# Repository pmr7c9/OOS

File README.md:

# OOS
	OOS - optyczny odbiornik sygnałów
	Urządzenie do odbioru sygnału optycznego i konwersję na sygnał elektryczny.

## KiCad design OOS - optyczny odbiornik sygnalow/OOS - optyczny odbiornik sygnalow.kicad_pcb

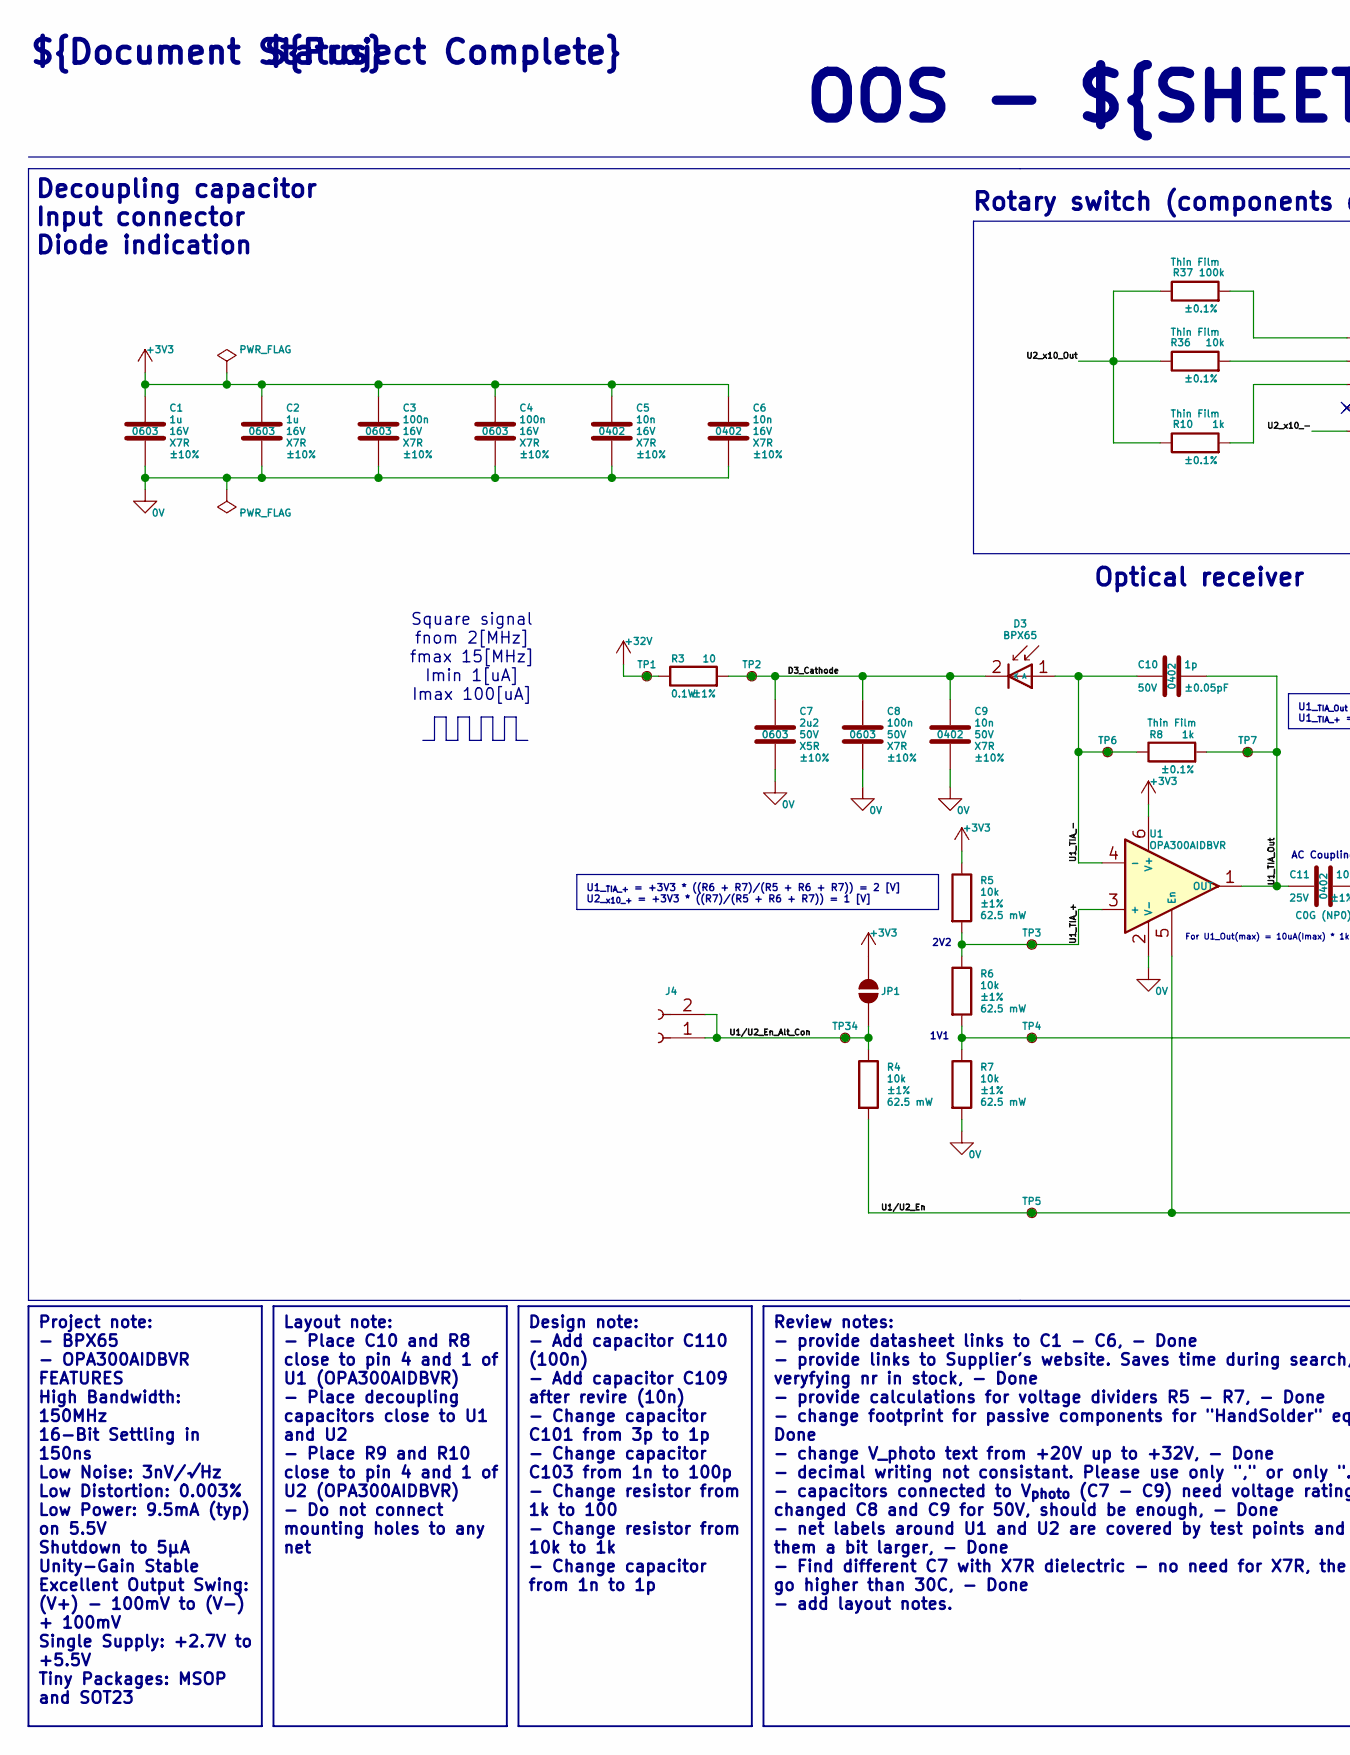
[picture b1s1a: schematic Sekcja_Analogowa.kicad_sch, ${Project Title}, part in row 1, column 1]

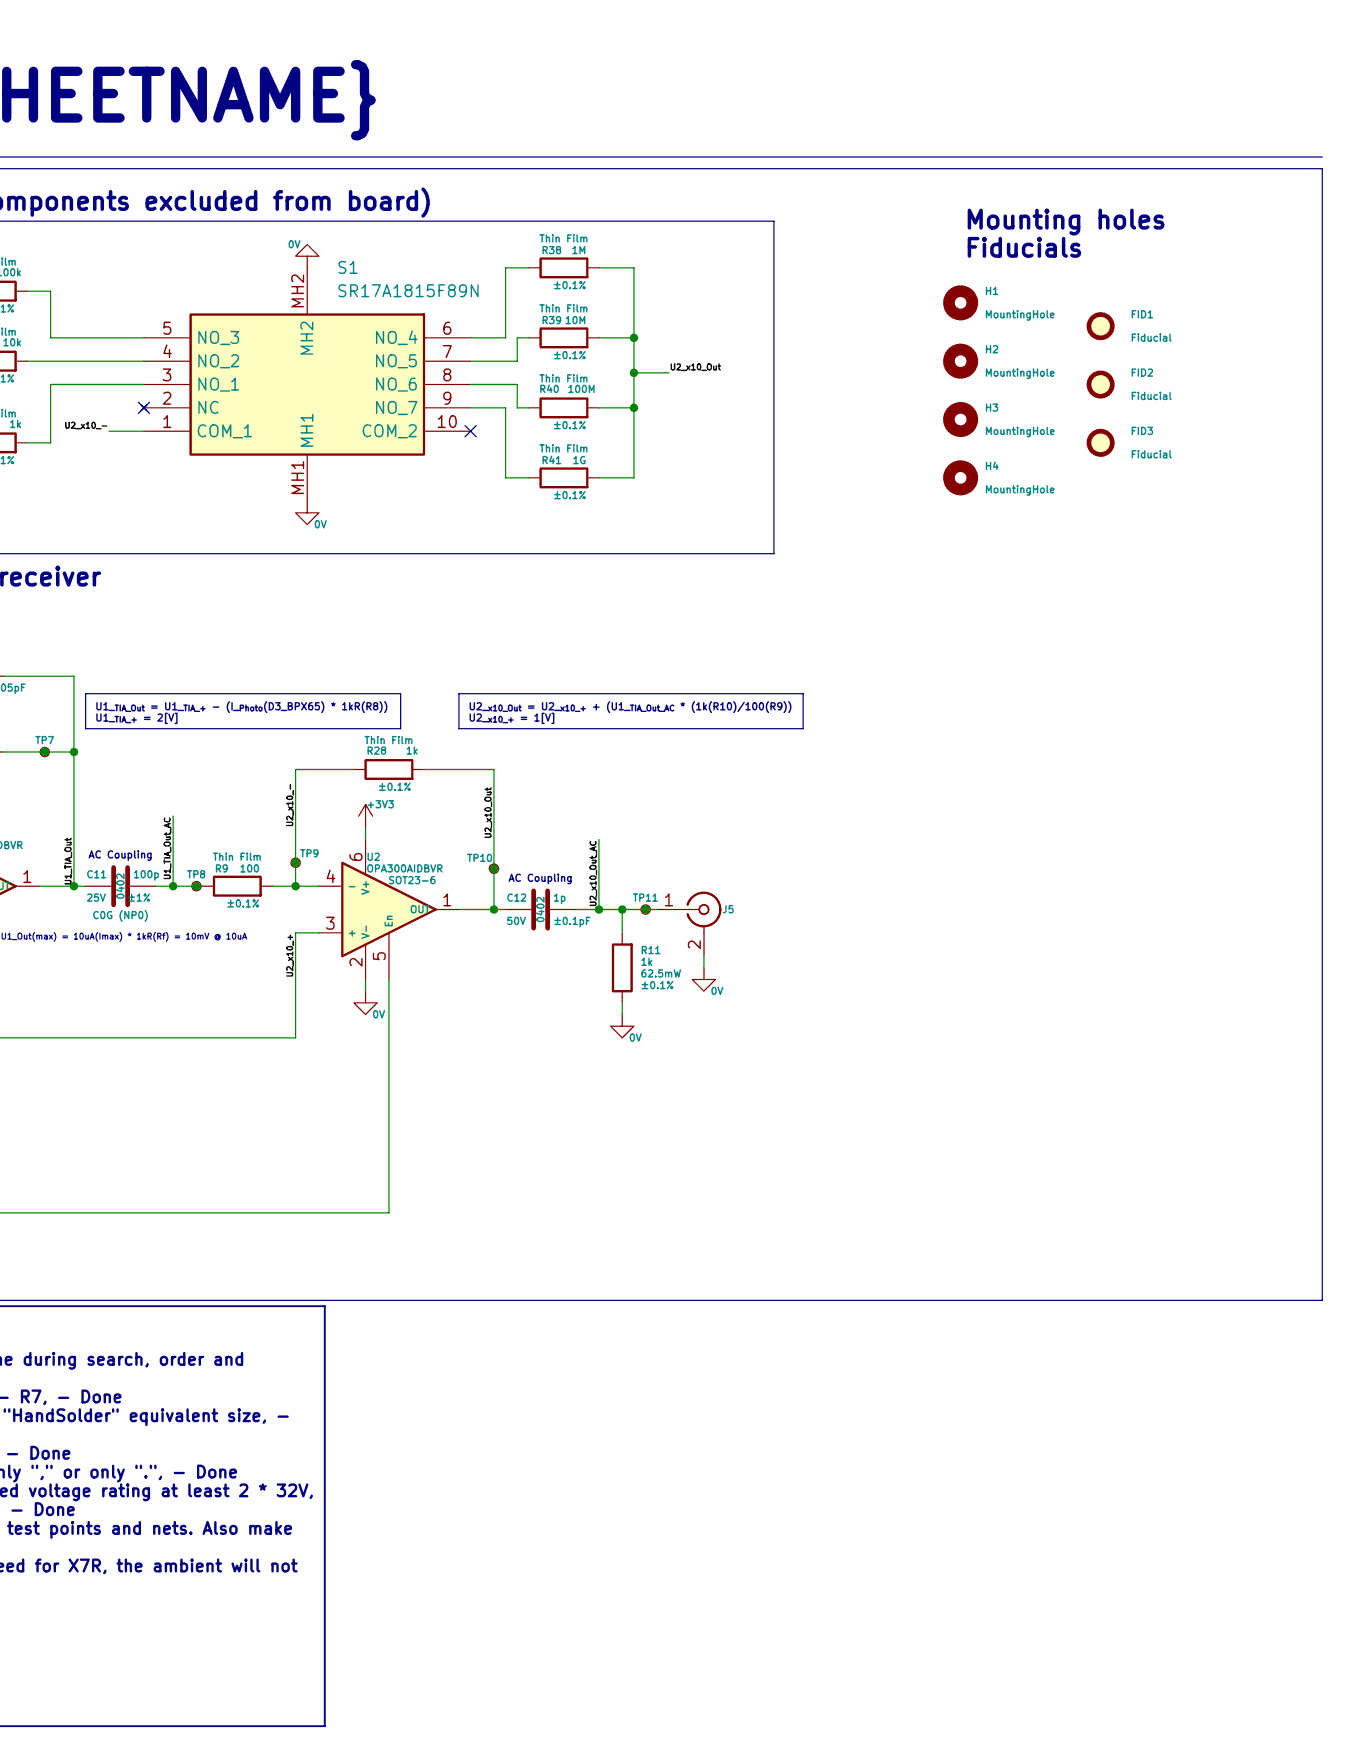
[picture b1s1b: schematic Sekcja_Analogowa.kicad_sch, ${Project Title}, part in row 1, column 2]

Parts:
C1, C2: 1u; C_0603_1608Metric_Pad1.08x0.95mm_HandSolder; Voltage Rating 16V; Tolerance ±10%; MPN CC0603KRX7R7BB105
C3, C4: 100n; C_0603_1608Metric_Pad1.08x0.95mm_HandSolder; Voltage Rating 16V; Tolerance ±10%; MPN CL10B104KO8WPNC
C5, C6: 10n; C_0402_1005Metric_Pad0.74x0.62mm_HandSolder; Voltage Rating 16V; Tolerance ±10%; MPN CL05B103KO5NNNC
C7: 2u2; C_0603_1608Metric_Pad1.08x0.95mm_HandSolder; Voltage Rating 50V; Tolerance ±10%; MPN GRT188R61H225KE13D
C8: 100n; C_0603_1608Metric_Pad1.08x0.95mm_HandSolder; Voltage Rating 50V; Tolerance ±10%; MPN CGA3E2X7R1H104KAA
C9: 10n; C_0402_1005Metric_Pad0.74x0.62mm_HandSolder; Voltage Rating 50V; Tolerance ±10%; MPN CL05B103KB5NNND
C10: 1p; C_0402_1005Metric_Pad0.74x0.62mm_HandSolder; Voltage Rating 50V; Tolerance ±0.05pF; MPN GCM1555C1H1R0BA16D
C11: 100p; C_0402_1005Metric_Pad0.74x0.62mm_HandSolder; Voltage Rating 25V; Tolerance ±1%; MPN GRM0225C1E101GA02L
C12: 1p; C_0402_1005Metric_Pad0.74x0.62mm_HandSolder; Voltage Rating 50V; Tolerance ±0.1pF; MPN GCM1555C1H1R0BA16D
D3: BPX65; TO-18-2_Lens; MPN BPX65
FID1, FID2, FID3: Fiducial; Fiducial_1.5mm_Mask3mm
H1, H2, H3, H4: MountingHole; MountingHole_3.2mm_M3
J4: Conn_01x02_Socket; PinHeader_1x02_P2.54mm_Vertical
J5: Conn_Coaxial; BNC_Amphenol_B6252HB-NPP3G-50_Horizontal; MPN R-128
JP1: SolderJumper_2_Open; SolderJumper-2_P1.3mm_Open_RoundedPad1.0x1.5mm
R3: 10; R_0603_1608Metric_Pad0.98x0.95mm_HandSolder; Power Rating 0.1W; Tolerance ±1%; MPN RCA060310R0FKEA
R4, R5, R6, R7: 10k; R_0402_1005Metric_Pad0.72x0.64mm_HandSolder; Power Rating 62.5 mW; Tolerance ±1%; MPN WR04X1002FTL
R8, R10, R11, R28: 1k; R_0402_1005Metric_Pad0.72x0.64mm_HandSolder; Power Rating 62.5mW; Tolerance ±0.1%; MPN RT0402BRD071KL
R9: 100; R_0402_1005Metric_Pad0.72x0.64mm_HandSolder; Power Rating 62.5mW; Tolerance ±0.1%; MPN ERA2AEB101X
R36: 10k; R_0402_1005Metric_Pad0.72x0.64mm_HandSolder; Power Rating 62.5mW; Tolerance ±0.1%; MPN RT0402BRD071KL
R37: 100k; R_0402_1005Metric_Pad0.72x0.64mm_HandSolder; Power Rating 62.5mW; Tolerance ±0.1%; MPN RT0402BRD071KL
R38: 1M; R_0402_1005Metric_Pad0.72x0.64mm_HandSolder; Power Rating 62.5mW; Tolerance ±0.1%; MPN RT0402BRD071KL
R39: 10M; R_0402_1005Metric_Pad0.72x0.64mm_HandSolder; Power Rating 62.5mW; Tolerance ±0.1%; MPN RT0402BRD071KL
R40: 100M; R_0402_1005Metric_Pad0.72x0.64mm_HandSolder; Power Rating 62.5mW; Tolerance ±0.1%; MPN RT0402BRD071KL
R41: 1G; R_0402_1005Metric_Pad0.72x0.64mm_HandSolder; Power Rating 62.5mW; Tolerance ±0.1%; MPN RT0402BRD071KL
S1: SR17A1815F89N; Manufacturer_Part_Number SR17A1815F89N
TP1, TP2, TP3, TP4, TP5, TP6, TP7, TP8, TP9, TP10, TP11, TP34: TestPoint_Small; TestPoint_Pad_D1.0mm
U1, U2: OPA300AIDBVR; SOT-23-6_Handsoldering; MPN OPA300AIDBVR

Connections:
0V: C1.2, C2.2, C3.2, C4.2, C5.2, C6.2, C7.1, C8.2, C9.2, J5.2 (Ext), R7.2, R11.1, S1.MH1, S1.MH2, U1.2 (V-), U2.2 (V-); also elsewhere on the board
+3V3: C1.1, C2.1, C3.1, C4.1, C5.1, C6.1, JP1.2 (B), R5.1, U1.6 (V+), U2.6 (V+); also elsewhere on the board
+32V: R3.1, TP1.1; also elsewhere on the board
/Sekcja_Analogowa/D3_Cathode: C7.2, C8.1, C9.1, D3.2 (K), R3.2, TP2.1
/Sekcja_Analogowa/U1_TIA_+: R5.2, R6.1, TP3.1, U1.3 (+)
/Sekcja_Analogowa/U1_TIA_-: C10.1, D3.1 (A), R8.1, TP6.1, U1.4 (-)
/Sekcja_Analogowa/U1_TIA_Out: C10.2, C11.1, R8.2, TP7.1, U1.1 (OUT)
/Sekcja_Analogowa/U1_TIA_Out_AC: C11.2, R9.1, TP8.1
/Sekcja_Analogowa/U1/U2_En: R4.2, TP5.1, U1.5 (En), U2.5 (En)
/Sekcja_Analogowa/U1/U2_En_Alt_Con: J4.1, J4.2, JP1.1 (A), R4.1, TP34.1
/Sekcja_Analogowa/U2_x10_+: R6.2, R7.1, TP4.1, U2.3 (+)
/Sekcja_Analogowa/U2_x10_-: R9.2, R28.1, S1.1 (COM_1), TP9.1, U2.4 (-)
/Sekcja_Analogowa/U2_x10_Out: C12.1, R10.1, R28.2, R36.1, R37.1, R38.2, R39.2, R40.2, R41.2, TP10.1, U2.1 (OUT)
/Sekcja_Analogowa/U2_x10_Out_AC: C12.2, J5.1 (In), R11.2, TP11.1
unnamed: R10.2, S1.3 (NO_1)
unnamed: R36.2, S1.4 (NO_2)
unnamed: R37.2, S1.5 (NO_3)
unnamed: R38.1, S1.6 (NO_4)
unnamed: R39.1, S1.7 (NO_5)
unnamed: R40.1, S1.8 (NO_6)
unnamed: R41.1, S1.9 (NO_7)

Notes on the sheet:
Square signal fnom 2[MHz] fmax 15[MHz] Imin 1[uA] Imax 100[uA]
For U1_Out(max) = 10uA(Imax) * 1kR(Rf) = 10mV @ 10uA
Mounting holes Fiducials
AC Coupling
1V1
${Project Complete}
${Document Status}
Decoupling capacitor Input connector Diode indication
OOS - ${SHEETNAME}
2V2
Optical receiver
Rotary switch (components excluded from board)
Review notes: - provide datasheet links to C1 - C6, - Done - provide links to Supplier's website. Saves time during search, order and veryfying nr in stock, - Done - provide calculations for voltage dividers R5 - R7, - Done - change footprint for passive components for "HandSolder" equivalent size,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
U2__{x10_Out} = U2__{x10_+} + (U1__{TIA_Out_AC} * (1k(R10)/100(R9)) U2__{x10_+} = 1[V]
Design note: - Add capacitor C110 (100n) - Add capacitor C109 after revire (10n) - Change capacitor C101 from 3p to 1p - Change capacitor C103 from 1n to 100p - Change resistor from 1k to 100 - Change resistor from 10k to 1k - Change capacitor from 1n to 1p
U1__{TIA_+} = +3V3 * ((R6 + R7)/(R5 + R6 + R7)) = 2 [V] U2__{x10_+} = +3V3 * ((R7)/(R5 + R6 + R7)) = 1 [V]
U1__{TIA_Out} = U1__{TIA_+} - (I__{Photo}(D3_BPX65) * 1kR(R8)) U1__{TIA_+} = 2[V]
Layout note: - Place C10 and R8 close to pin 4 and 1 of U1 (OPA300AIDBVR) - Place decoupling capacitors close to U1 and U2 - Place R9 and R10 close to pin 4 and 1 of U2 (OPA300AIDBVR) - Do not connect mounting holes to any net
Project note: - BPX65 - OPA300AIDBVR FEATURES High Bandwidth: 150MHz 16-Bit Settling in 150ns Low Noise: 3nV/√Hz Low Distortion: 0.003% Low Power: 9.5mA (typ) on 5.5V Shutdown to 5μA Unity-Gain Stable Excellent Output Swing: (V+) − 100mV to (V−) + 100mV Single Supply: +2.7V to +5.5V Tiny Packages: 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

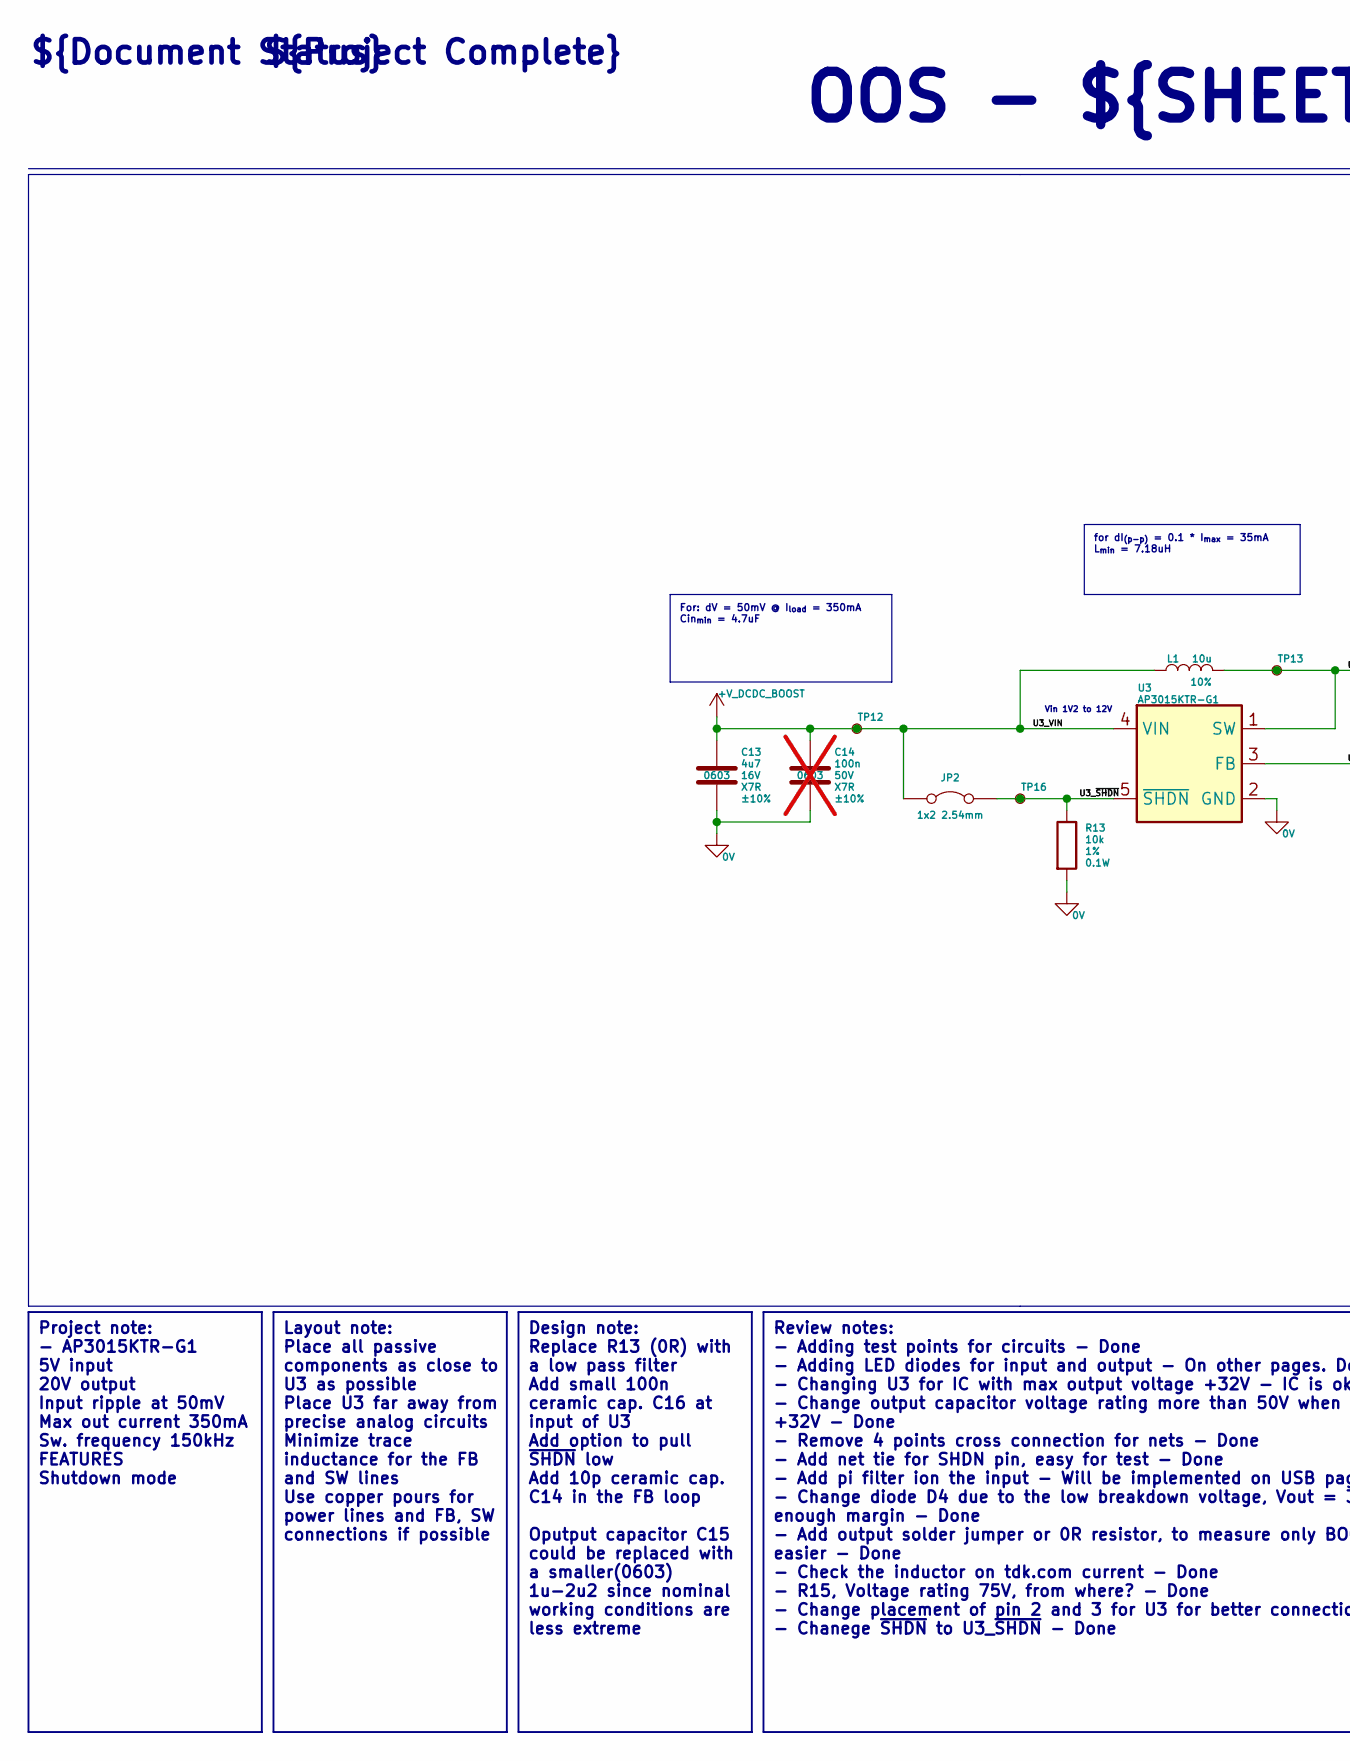
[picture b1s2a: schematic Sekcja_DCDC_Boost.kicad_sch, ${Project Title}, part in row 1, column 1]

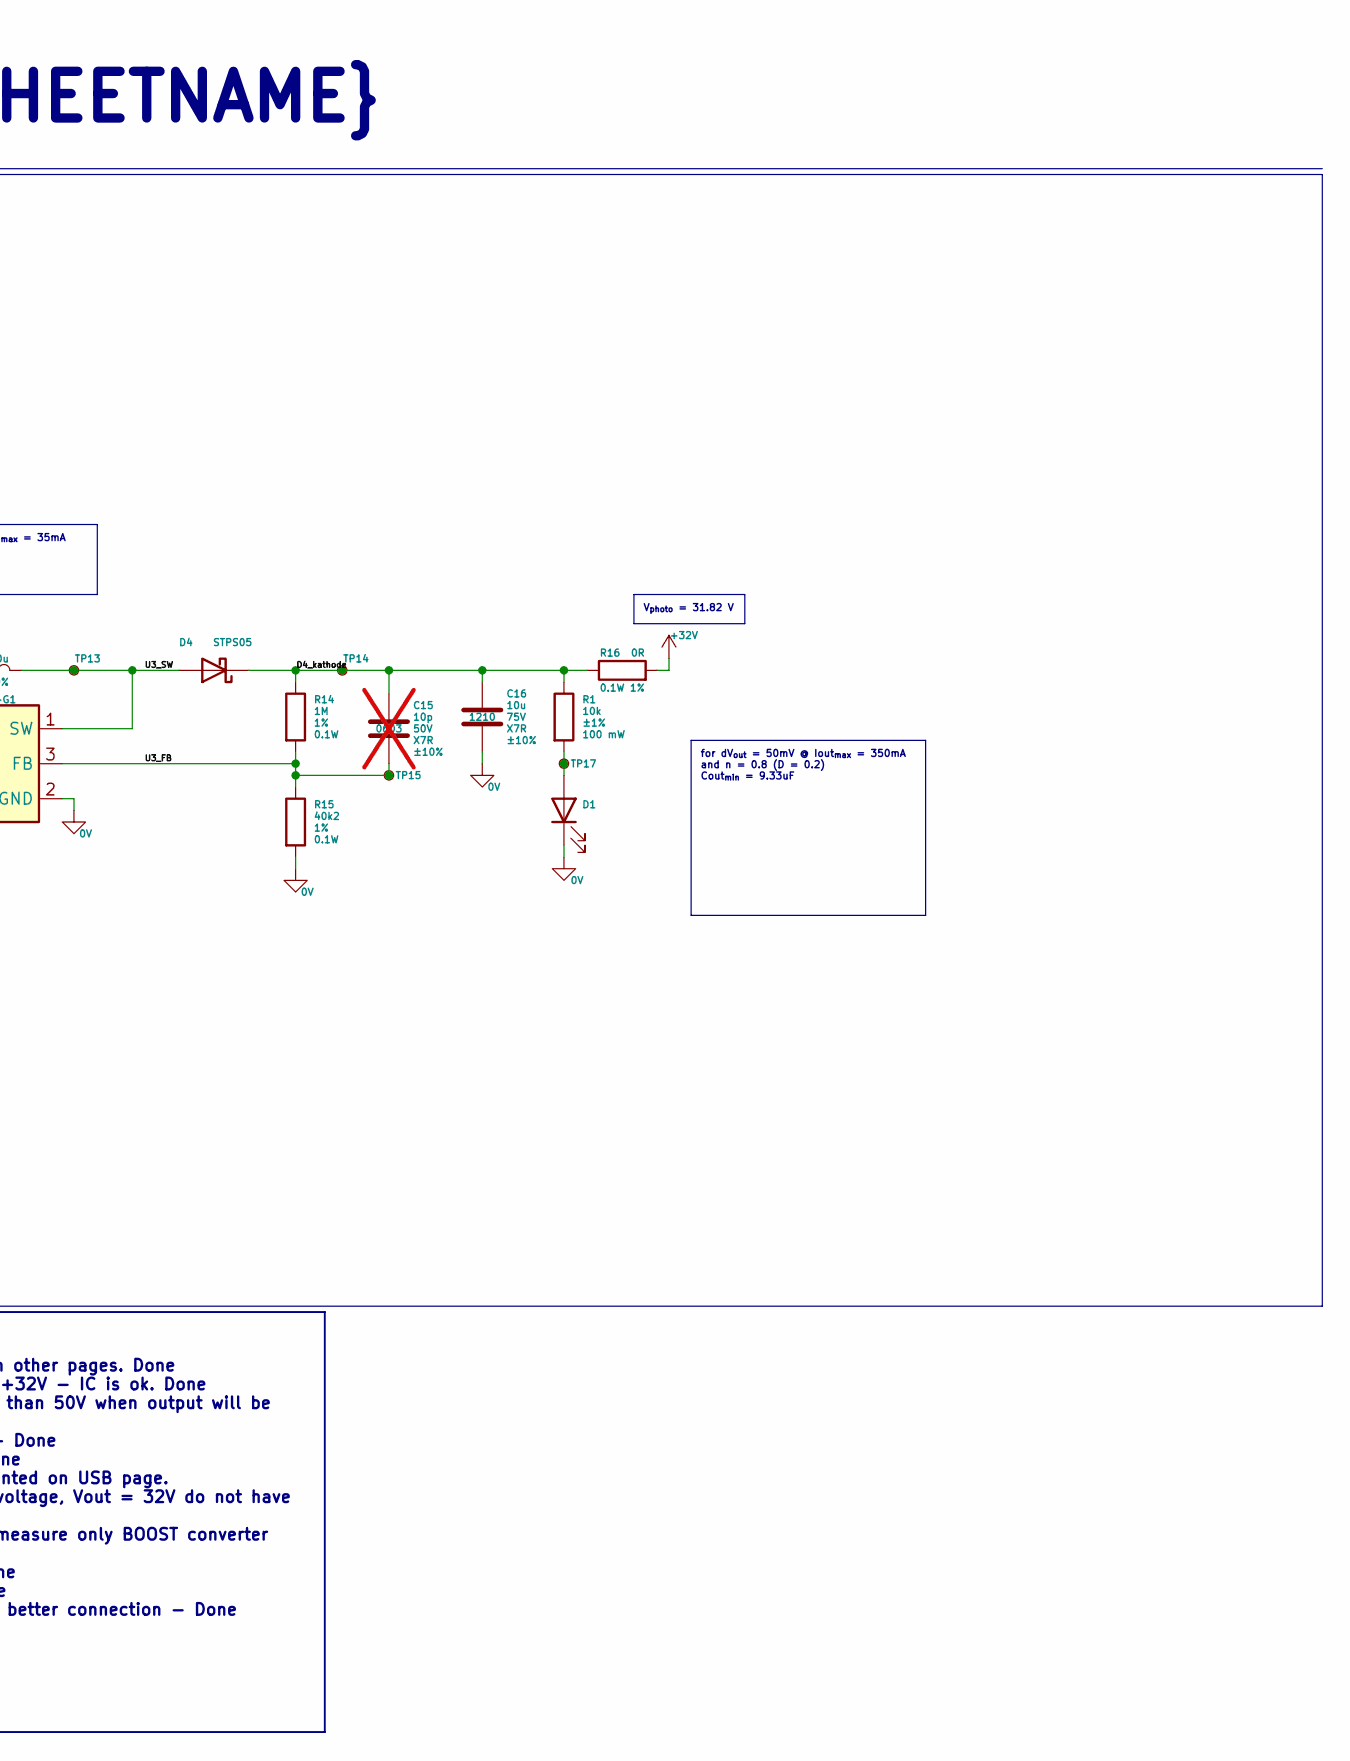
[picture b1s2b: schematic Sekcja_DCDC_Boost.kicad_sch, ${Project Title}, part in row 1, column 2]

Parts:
C13: 4u7; C_0603_1608Metric; Voltage Rating 16V; Tolerance ±10%
C14: 100n; C_0603_1608Metric; Voltage Rating 50V; Tolerance ±10%; not fitted
C15: 10p; C_0603_1608Metric; Voltage Rating 50V; Tolerance ±10%; not fitted
C16: 10u; C_1210_3225Metric_Pad1.33x2.70mm_HandSolder; Voltage Rating 75V; Tolerance ±10%
D1: LED; D_0603_1608Metric_Pad1.05x0.95mm_HandSolder; MPN LTST-C191KGKT
D4: STPS05; Nexperia_CFP3_SOD-123W
JP2: 1x2 2.54mm; PinHeader_1x02_P2.54mm_Vertical
L1: 10u; L_1210_3225Metric_Pad1.42x2.65mm_HandSolder; Tolerance 10%
R1: 10k; R_0603_1608Metric_Pad0.98x0.95mm_HandSolder; Power Rating 100 mW; Tolerance ±1%; MPN RC0603FR-0710K
R13: 10k; R_0603_1608Metric; Power Rating 0.1W; Tolerance 1%
R14: 1M; R_0603_1608Metric; Power Rating 0.1W; Tolerance 1%
R15: 40k2; R_0603_1608Metric; Power Rating 0.1W; Tolerance 1%
R16: 0R; R_0603_1608Metric; Power Rating 0.1W; Tolerance 1%
TP12, TP13, TP14, TP15, TP16, TP17: TestPoint_Small; TestPoint_Pad_D1.0mm
U3: AP3015KTR-G1; SOT-23-5_HandSoldering

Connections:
0V: C13.2, C14.2, C16.2, D1.1 (K), R13.2, R15.2, U3.2 (GND); also elsewhere on the board
+32V: R16.2; also elsewhere on the board
+V_DCDC_BOOST: C13.1, C14.1, JP2.1 (A), L1.1, TP12.1, U3.4 (VIN); also elsewhere on the board
/Sekcja_DCDC_Boost/D4_kathode: C15.1, C16.1, D4.1 (K), R1.1, R14.1, R16.1, TP14.1
/Sekcja_DCDC_Boost/U3_FB: C15.2, R14.2, R15.1, TP15.1, U3.3 (FB)
/Sekcja_DCDC_Boost/U3_SW: D4.2 (A), L1.2, TP13.1, U3.1 (SW)
/Sekcja_DCDC_Boost/U3_~SHDN: JP2.2 (B), R13.1, TP16.1, U3.5 (~SHDN)
unnamed: D1.2 (A), R1.2, TP17.1

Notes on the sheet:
${Document Status}
Vin 1V2 to 12V
OOS - ${SHEETNAME}
${Project Complete}
for dV_{out} = 50mV @ Iout_{max} = 350mA and n = 0.8 (D = 0.2) Cout_{min} = 9.33uF
Project note: - AP3015KTR-G1 5V input 20V output Input ripple at 50mV Max out current 350mA Sw. frequency 150kHz FEATURES Shutdown mode
V_{photo} = 31.82 V
Layout note: Place all passive components as close to U3 as possible Place U3 far away from precise analog circuits Minimize trace inductance for the FB and SW lines Use copper pours for power lines and FB, SW connections if possible
For: dV = 50mV @ I_{load} = 350mA Cin_{min} = 4.7uF
for dI_{(p-p)} = 0.1 * I_{max} = 35mA L_{min} = 7.18uH
Design note: Replace R13 (0R) with a low pass filter Add small 100n ceramic cap. C16 at input of U3 Add option to pull ~{SHDN} low Add 10p ceramic cap. C14 in the FB loop Oputput capacitor C15 could be replaced with a smaller(0603) 1u-2u2 since nominal working conditions are less extreme
Review notes: - Adding test points for circuits - Done - Adding LED diodes for input and output - On other pages. Done - Changing U3 for IC with max output voltage +32V - IC is ok. Done - Change output capacitor voltage rating more than 50V when output will be +32V - Done - Remove 4 points cross co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

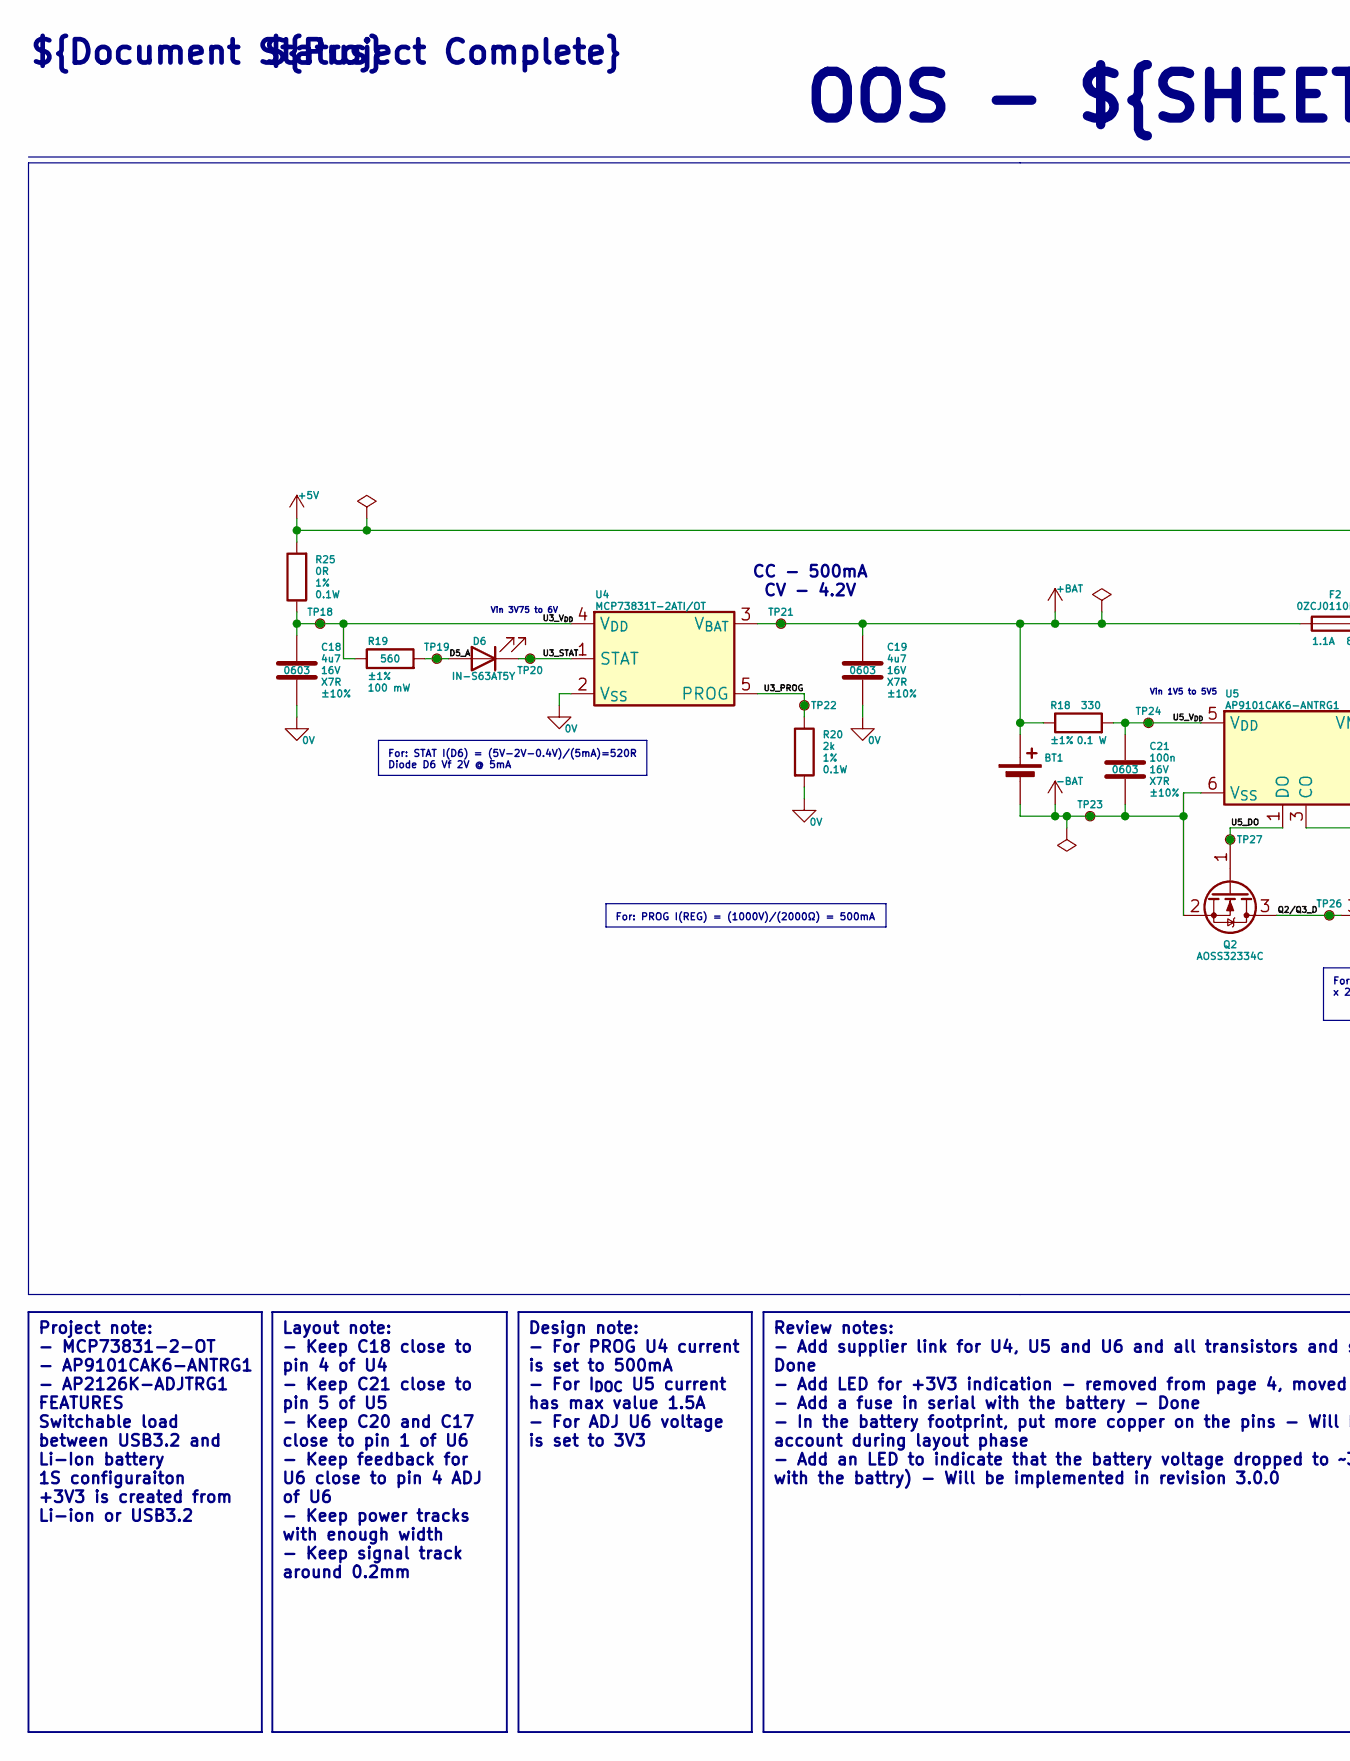
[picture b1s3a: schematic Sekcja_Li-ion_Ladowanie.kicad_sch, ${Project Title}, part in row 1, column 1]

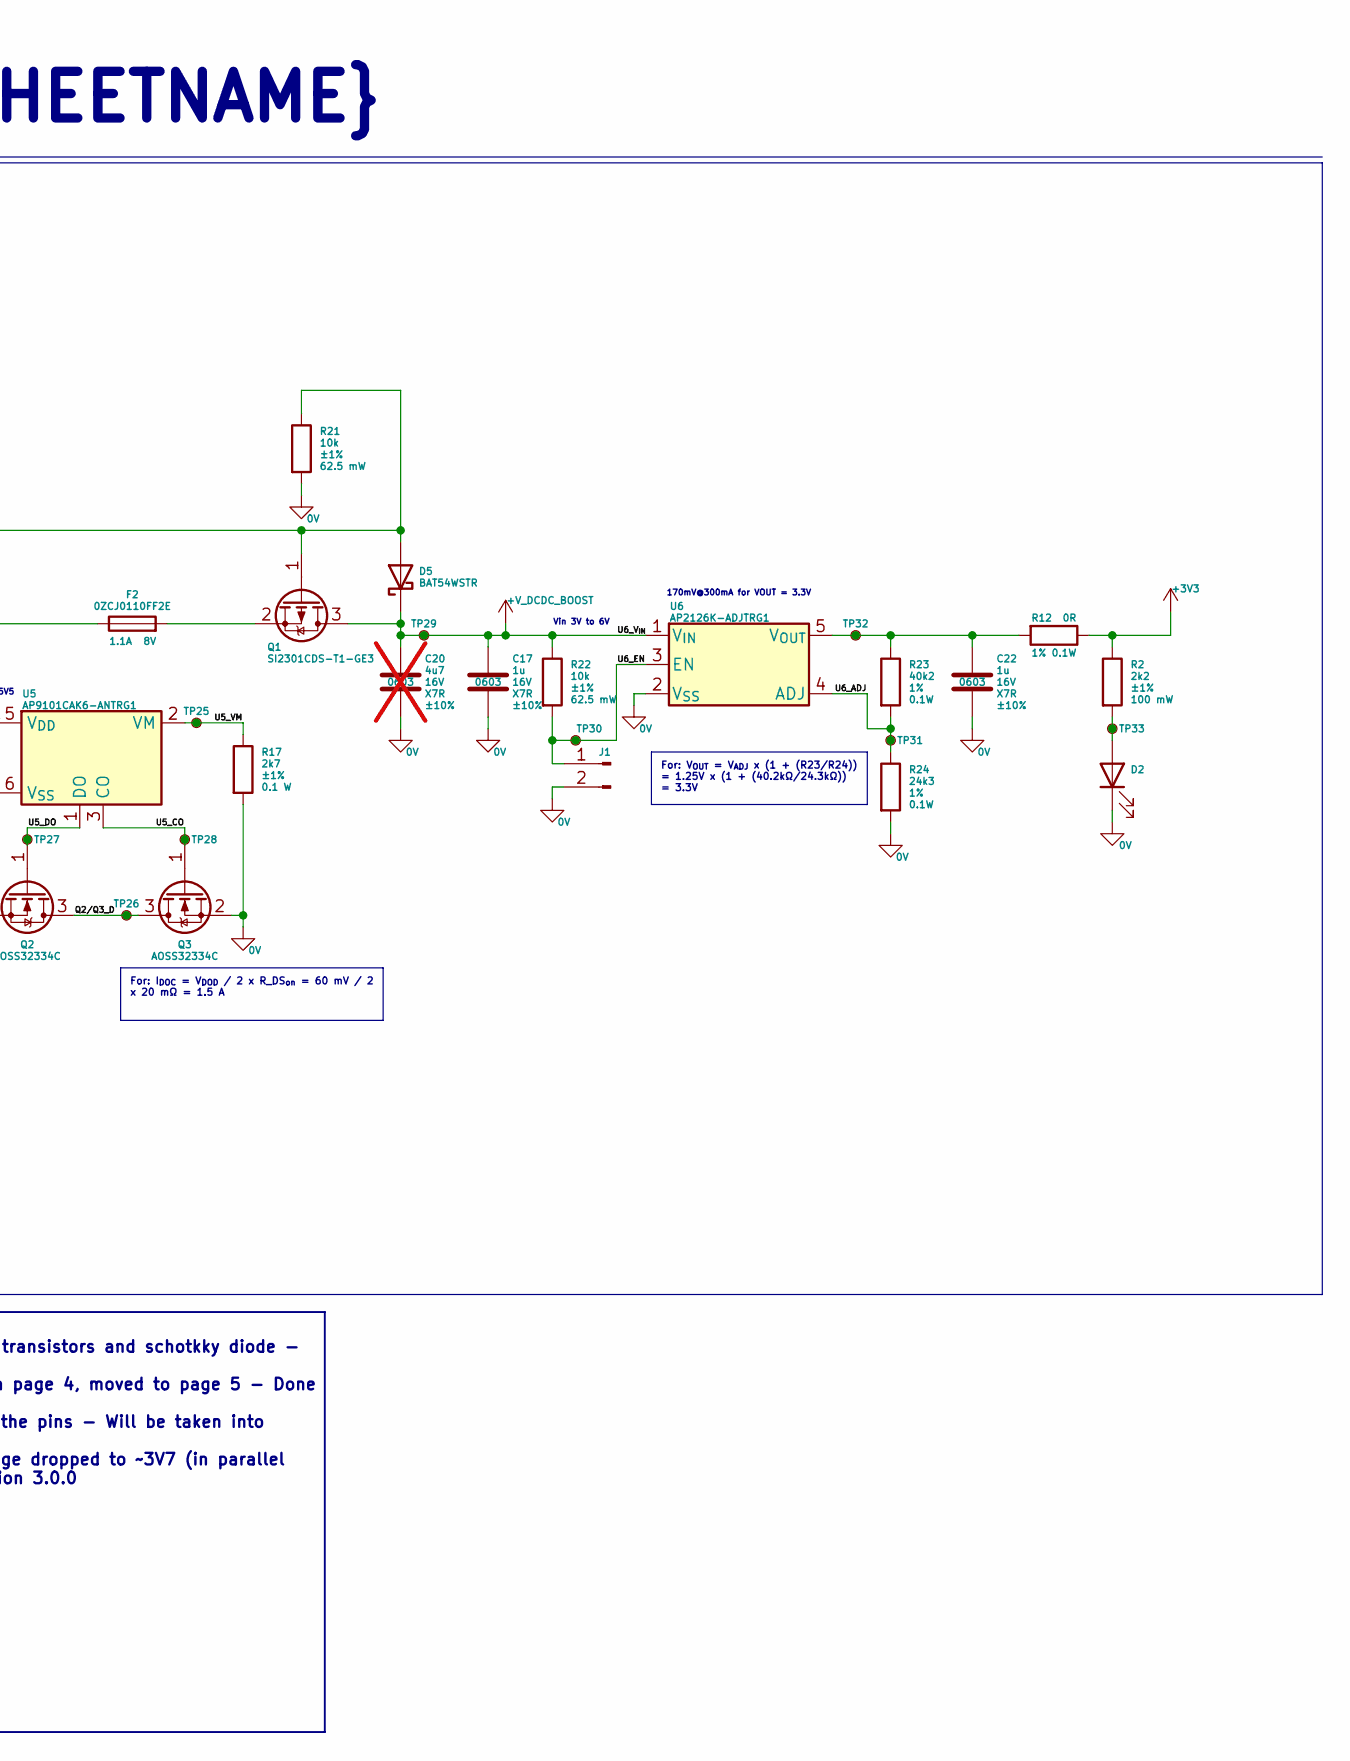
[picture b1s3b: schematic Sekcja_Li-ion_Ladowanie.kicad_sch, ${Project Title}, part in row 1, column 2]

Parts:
BT1: Battery_Cell; BatteryHolder_MPD_BH-18650-PC2
C17, C22: 1u; C_0603_1608Metric_Pad1.08x0.95mm_HandSolder; Voltage Rating 16V; Tolerance ±10%; MPN CC0603KRX7R7BB105
C18, C19: 4u7; C_0603_1608Metric; Voltage Rating 16V; Tolerance ±10%
C20: 4u7; C_0603_1608Metric; Voltage Rating 16V; Tolerance ±10%; not fitted
C21: 100n; C_0603_1608Metric_Pad1.08x0.95mm_HandSolder; Voltage Rating 16V; Tolerance ±10%; MPN CL10B104KO8WPNC
D2: LED; D_0603_1608Metric_Pad1.05x0.95mm_HandSolder; MPN LTST-C191KGKT
D5: BAT54WSTR; D_SOD-323
D6: LED; D_0603_1608Metric_Pad1.05x0.95mm_HandSolder; MPN IN-S63AT5Y
F2: 0ZCJ0110FF2E; Fuse_1206_3216Metric; Max Voltage 8V
J1: Conn_01x02_Pin; PinHeader_1x02_P2.54mm_Vertical
Q1: SI2301CDS-T1-GE3; SOT-23_Handsoldering
Q2, Q3: AOSS32334C; SOT-23
R2: 2k2; R_0603_1608Metric_Pad0.98x0.95mm_HandSolder; Power Rating 100 mW; Tolerance ±1%; MPN AC0603FR-072K2L
R12, R25: 0R; R_0603_1608Metric; Power Rating 0.1W; Tolerance 1%
R17: 2k7; R_0603_1608Metric_Pad0.98x0.95mm_HandSolder; Power Rating 0.1 W; Tolerance ±1%; MPN ERJ3EKF2701V
R18: 330; R_0603_1608Metric_Pad0.98x0.95mm_HandSolder; Power Rating 0.1 W; Tolerance ±1%; MPN RC0603FR-07330RL
R19: 560; R_0603_1608Metric_Pad0.98x0.95mm_HandSolder; Power Rating 100 mW; Tolerance ±1%; MPN WR06X5600FTL
R20: 2k; R_0603_1608Metric_Pad0.98x0.95mm_HandSolder; Power Rating 0.1W; Tolerance 1%
R21, R22: 10k; R_0402_1005Metric_Pad0.72x0.64mm_HandSolder; Power Rating 62.5 mW; Tolerance ±1%; MPN WR04X1002FTL
R23: 40k2; R_0603_1608Metric; Power Rating 0.1W; Tolerance 1%
R24: 24k3; R_0603_1608Metric; Power Rating 0.1W; Tolerance 1%; MPN ERJ3EKF2432V
TP18, TP19, TP20, TP21, TP22, TP23, TP24, TP25, TP26, TP27, TP28, TP29, TP30, TP31, TP32, TP33: TestPoint_Small; TestPoint_Pad_D1.0mm
U4: MCP73831T-2ATI/OT; SOT-23-5
U5: AP9101CAK6-ANTRG1; SOT-23-6
U6: AP2126K-ADJTRG1; SOT-23-5_HandSoldering

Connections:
0V: C17.2, C18.2, C19.2, C20.2, C22.2, D2.1 (K), J1.2, Q3.2 (S), R17.2, R20.2, R21.2, R24.2, U4.2 (V_{SS}), U6.2 (V_{SS}); also elsewhere on the board
+3V3: R2.1, R12.1; also elsewhere on the board
+5V: D5.2 (A), Q1.1 (G), R21.1, R25.2; also elsewhere on the board
+BAT: BT1.1 (+), C19.1, F2.1, R18.1, TP21.1, U4.3 (V_{BAT})
+V_DCDC_BOOST: C17.1, C20.1, D5.1 (K), Q1.3 (D), R22.1, TP29.1, U6.1 (V_{IN}); also elsewhere on the board
-BAT: BT1.2 (-), C21.2, Q2.2 (S), TP23.1, U5.6 (V_{SS})
/Sekcja_Li-ion_Ladowanie/D5_A: D6.2 (A), R19.2, TP19.1
/Sekcja_Li-ion_Ladowanie/Q2/Q3_D: Q2.3 (D), Q3.3 (D), TP26.1
/Sekcja_Li-ion_Ladowanie/U3_PROG: R20.1, TP22.1, U4.5 (PROG)
/Sekcja_Li-ion_Ladowanie/U3_STAT: D6.1 (K), TP20.1, U4.1 (STAT)
/Sekcja_Li-ion_Ladowanie/U3_V_{DD}: C18.1, R19.1, R25.1, TP18.1, U4.4 (V_{DD})
/Sekcja_Li-ion_Ladowanie/U5_CO: Q3.1 (G), TP28.1, U5.3 (CO)
/Sekcja_Li-ion_Ladowanie/U5_DO: Q2.1 (G), TP27.1, U5.1 (DO)
/Sekcja_Li-ion_Ladowanie/U5_VM: R17.1, TP25.1, U5.2 (VM)
/Sekcja_Li-ion_Ladowanie/U5_V_{DD}: C21.1, R18.2, TP24.1, U5.5 (V_{DD})
/Sekcja_Li-ion_Ladowanie/U6_ADJ: R23.2, R24.1, TP31.1, U6.4 (ADJ)
/Sekcja_Li-ion_Ladowanie/U6_EN: J1.1, R22.2, TP30.1, U6.3 (EN)
unnamed: D2.2 (A), R2.2, TP33.1
unnamed: F2.2, Q1.2 (S)
unnamed: C22.1, R12.2, R23.1, TP32.1, U6.5 (V_{OUT})

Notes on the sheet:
${Document Status}
Vin 1V5 to 5V5
Vin 3V to 6V
OOS - ${SHEETNAME}
Vin 3V75 to 6V
CC - 500mA CV - 4.2V
170mV@300mA for VOUT = 3.3V
${Project Complete}
Project note: - MCP73831-2-OT - AP9101CAK6-ANTRG1 - AP2126K-ADJTRG1 FEATURES Switchable load between USB3.2 and Li-Ion battery 1S configuraiton +3V3 is created from Li-ion or USB3.2
For: PROG I(REG) = (1000V)/(2000Ω) = 500mA
For: STAT I(D6) = (5V-2V-0.4V)/(5mA)=520R Diode D6 Vf 2V @ 5mA
For: I_{DOC} = V_{DOD} / 2 x R_DS_{on} = 60 mV / 2 x 20 mΩ = 1.5 A
Design note: - For PROG U4 current is set to 500mA - For I_{DOC} U5 current has max value 1.5A - For ADJ U6 voltage is set to 3V3
Layout note: - Keep C18 close to pin 4 of U4 - Keep C21 close to pin 5 of U5 - Keep C20 and C17 close to pin 1 of U6 - Keep feedback for U6 close to pin 4 ADJ of U6 - Keep power tracks with enough width - Keep signal track around 0.2mm
For: V_{OUT} = V_{ADJ} x (1 + (R23/R24)) = 1.25V x (1 + (40.2kΩ/24.3kΩ)) = 3.3V
Review notes: - Add supplier link for U4, U5 and U6 and all transistors and schotkky diode - Done - Add LED for +3V3 indication - removed from page 4, moved to page 5 - Done - Add a fuse in serial with the battery - Done - In the battery footprint, put more copper on the pins - Will be taken into a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
